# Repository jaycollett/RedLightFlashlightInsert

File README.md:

# RedLightFlashlightInsert
Replacement LED board for flashlights. Built with 670nm Red LEDs for Eye Treatments

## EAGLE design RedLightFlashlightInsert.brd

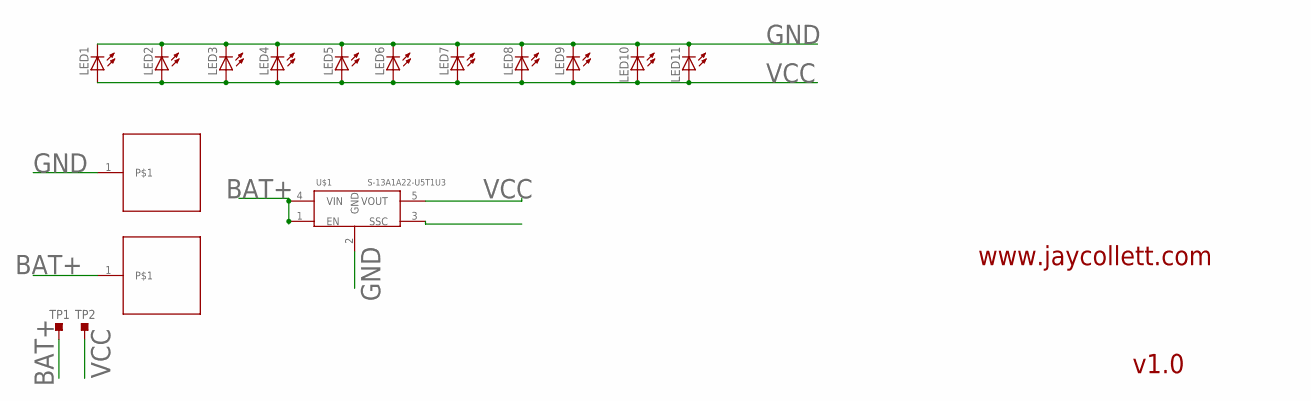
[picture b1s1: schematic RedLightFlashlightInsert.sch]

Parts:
LED1, LED2, LED3, LED4, LED5, LED6, LED7, LED8, LED9, LED10, LED11: LED5MM
TP1, TP2: TESTPOINT_TPS-SMD-10SN; TESTPOINT_SMD-10SN
U$1: S-13A1A22-U5T1U3; SOT-89-5
U$2, U$3: SOLDERPAD

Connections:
BAT+: TP1.TP, U$1.1 (EN), U$1.4 (VIN), U$3.1
GND: LED1.K (C), LED2.K (C), LED3.K (C), LED4.K (C), LED5.K (C), LED6.K (C), LED7.K (C), LED8.K (C), LED9.K (C), LED10.K (C), LED11.K (C), U$1.2 (GND), U$2.1
VCC: LED1.A, LED2.A, LED3.A, LED4.A, LED5.A, LED6.A, LED7.A, LED8.A, LED9.A, LED10.A, LED11.A, TP2.TP, U$1.5 (VOUT)

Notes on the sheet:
v1.0
www.jaycollett.com

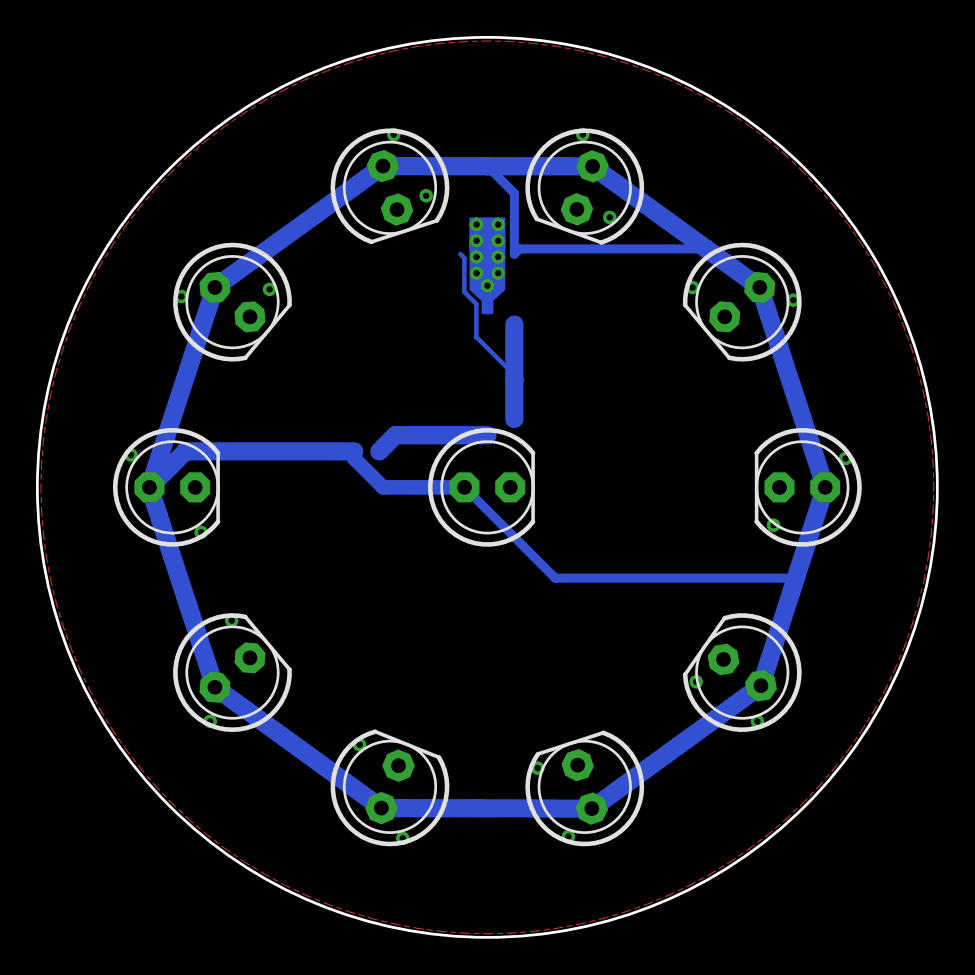
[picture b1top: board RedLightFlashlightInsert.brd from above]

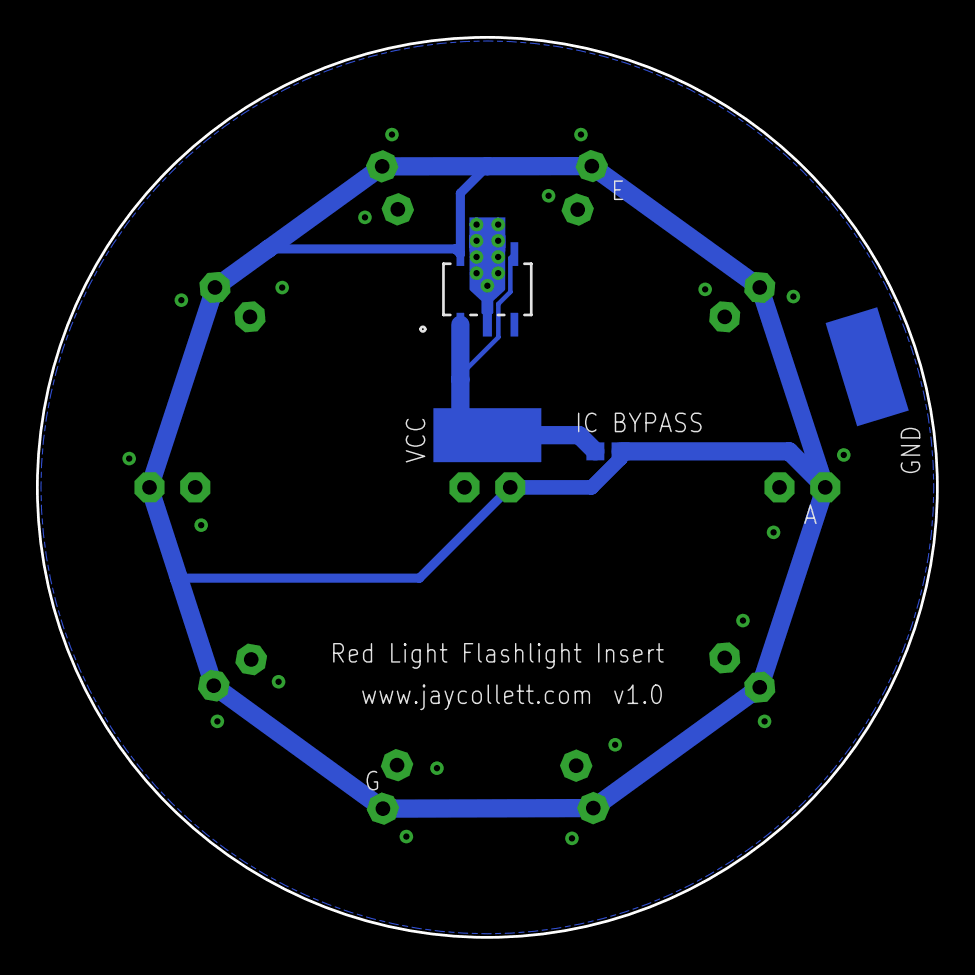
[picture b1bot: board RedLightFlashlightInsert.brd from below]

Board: 2 copper layers, 50.0 x 50.0 mm, 16 parts (5 on the bottom side), 3 nets.

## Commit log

2021-01-12 add initial board and schematic designs.
